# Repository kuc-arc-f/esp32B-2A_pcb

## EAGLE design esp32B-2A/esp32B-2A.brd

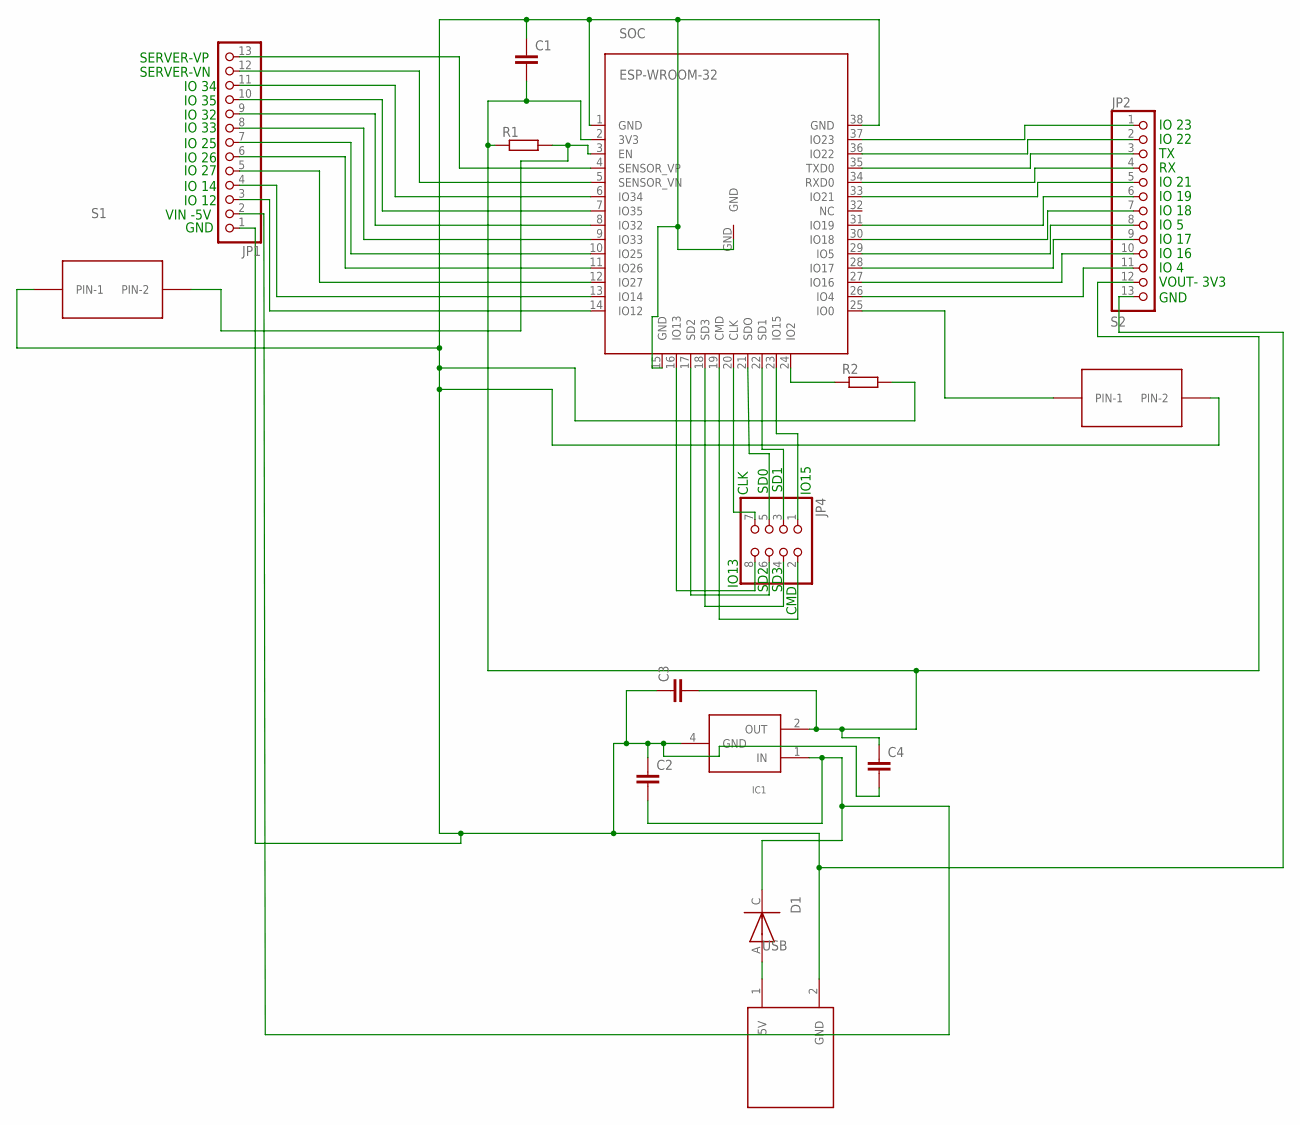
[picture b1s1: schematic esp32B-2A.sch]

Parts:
C1, C2: C-EUC0603; C0603
C3, C4: C-EUC1206; C1206
D1: DIODE-EX; SOD80C
IC1: NJM2845DL1; NJM2845DL1-PKG
JP1, JP2: PINHD-1X13; 1X13
JP4: PINHD-2X4; 2X04
R1, R2: R-EU_R0603; R0603
S1, S2: BTN2-EX; B3F-10XX
SOC: ESP-WROOM-32
USB: USB-CUST-1; USB-CUST-1-PKG

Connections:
unnamed: JP2.2, SOC.36 (IO22)
unnamed: S2.1 (PIN-1), SOC.25 (IO0)
unnamed: R2.1, SOC.24 (IO2)
unnamed: JP2.3, SOC.35 (TXD0)
unnamed: JP2.4, SOC.34 (RXD0)
unnamed: JP1.13, SOC.4 (SENSOR_VP)
unnamed: JP2.1, SOC.37 (IO23)
unnamed: JP4.8, SOC.16 (IO13)
unnamed: JP4.7, SOC.20 (CLK)
unnamed: JP2.5, SOC.33 (IO21)
unnamed: C1.2, C3.2, C4.1, IC1.2 (OUT), JP2.12, R1.1, SOC.2 (3V3)
unnamed: D1.A, USB.1 (5V)
unnamed: JP2.6, SOC.31 (IO19)
unnamed: JP2.7, SOC.30 (IO18)
unnamed: JP2.8, SOC.29 (IO5)
unnamed: JP2.9, SOC.28 (IO17)
unnamed: JP2.10, SOC.27 (IO16)
unnamed: JP2.11, SOC.26 (IO4)
unnamed: JP1.12, SOC.5 (SENSOR_VN)
unnamed: JP1.11, SOC.6 (IO34)
unnamed: JP1.10, SOC.7 (IO35)
unnamed: JP1.9, SOC.8 (IO32)
unnamed: JP1.8, SOC.9 (IO33)
unnamed: JP1.7, SOC.10 (IO25)
unnamed: JP1.6, SOC.11 (IO26)
unnamed: JP1.5, SOC.12 (IO27)
unnamed: JP4.5, SOC.21 (SDO)
unnamed: JP4.3, SOC.22 (SD1)
unnamed: JP4.2, SOC.19 (CMD)
unnamed: JP4.4, SOC.18 (SD3)
unnamed: JP4.6, SOC.17 (SD2)
unnamed: JP1.4, SOC.13 (IO14)
unnamed: JP1.3, SOC.14 (IO12)
unnamed: C1.1, C2.1, C3.1, C4.2, IC1.4 (GND), JP1.1, JP2.13, R2.2, S1.1 (PIN-1), S2.2 (PIN-2), SOC.1 (GND), SOC.15 (GND), SOC.38 (GND), SOC.GND, USB.2 (GND)
unnamed: C2.2, D1.C, IC1.1 (IN), JP1.2
unnamed: R1.2, S1.2 (PIN-2), SOC.3 (EN)
unnamed: JP4.1, SOC.23 (IO15)

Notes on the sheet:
GND
VOUT- 3V3
VIN -5V
IO 23
IO 22
IO 21
SERVER-VP
SERVER-VN
IO 34
IO 35
IO 32
IO 33
IO 25
IO 12
IO 14
IO 27
IO 26
IO 19
IO 18
IO 4
IO 16
IO 17
IO 5
IO13
SD2
SD3
CMD
CLK
SD0
SD1
IO15

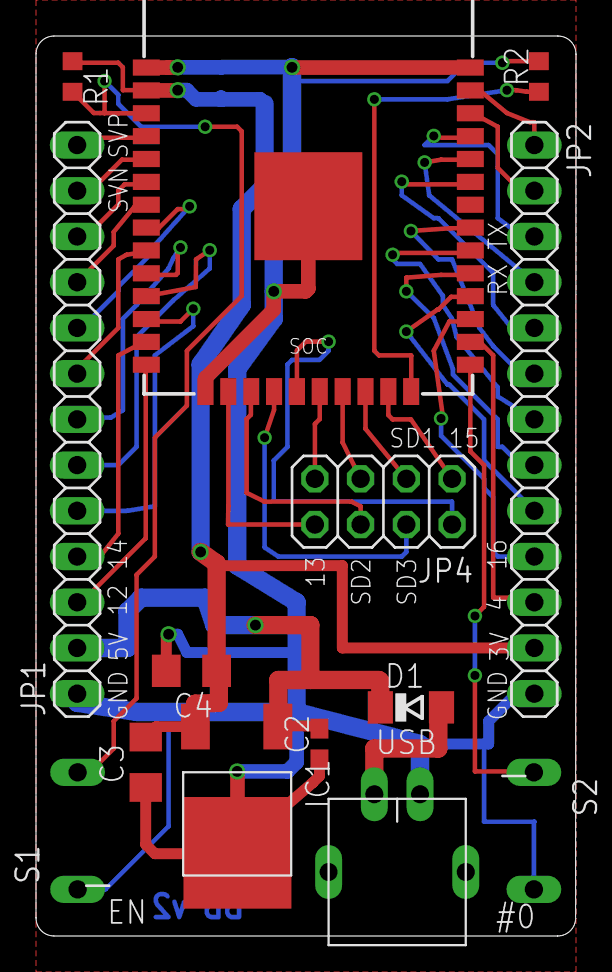
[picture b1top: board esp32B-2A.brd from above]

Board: 2 copper layers, 30.0 x 50.0 mm, 15 parts (1 on the bottom side), 37 nets.

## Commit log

2017-08-20 new, 08-20a1
